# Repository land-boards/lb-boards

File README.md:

lb-boards Designs
=================

land-boards.com - Printed Circuit Board Designs
-----------------------------------------------

Design files are kept here. Most are [Kicad based designs][Kicad].
[Kicad]: http://www.kicad-pcb.org/display/KICAD/KiCad+EDA+Software+Suite/ "Kicad is an open source electronic design suite which includes professional quality schematic capture and board layout tools."

See [our PCB Designs Website][ourWebsite] and our [land-boards Wiki][ourWiki].
[ourWebsite]: http://land-boards.com/content/ "land-boards.com website"
[ourWiki]: http://land-boards.com/blwiki/ "land-boards.com wiki"

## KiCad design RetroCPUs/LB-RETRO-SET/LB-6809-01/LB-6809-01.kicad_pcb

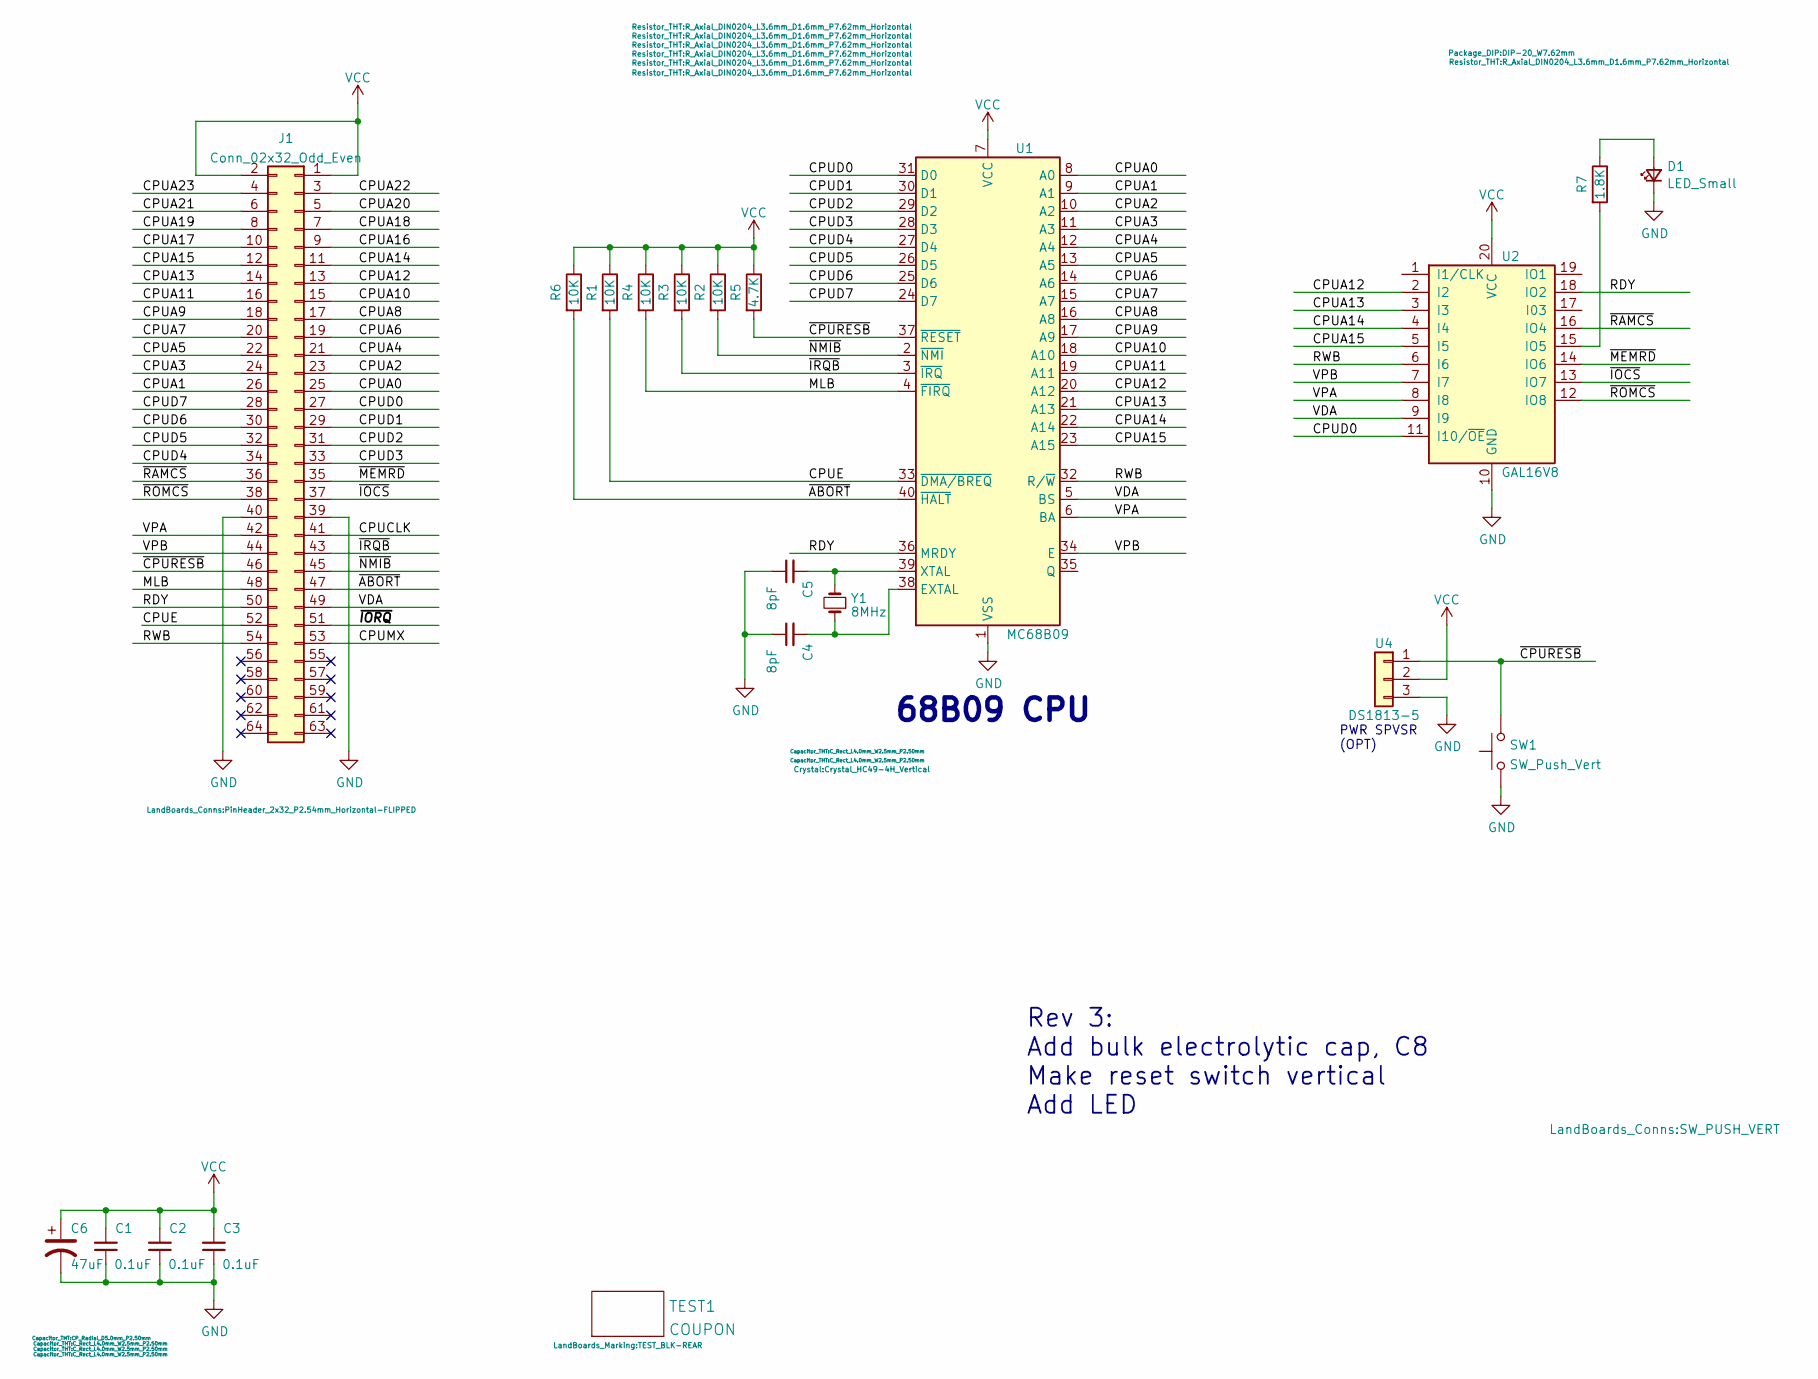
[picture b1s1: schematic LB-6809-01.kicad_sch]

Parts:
C1, C2, C3: 0.1uF; C_Rect_L4.0mm_W2.5mm_P2.50mm
C4, C5: 8pF; C_Rect_L4.0mm_W2.5mm_P2.50mm
C6: 47uF; CP_Radial_D5.0mm_P2.50mm
D1: LED_Small; LED_D5.0mm_Horizontal_O3.81mm_Z9.0mm
J1: Conn_02x32_Odd_Even; PinHeader_2x32_P2.54mm_Horizontal-FLIPPED
R1, R2, R3, R4, R6: 10K; R_Axial_DIN0204_L3.6mm_D1.6mm_P7.62mm_Horizontal
R5: 4.7K; R_Axial_DIN0204_L3.6mm_D1.6mm_P7.62mm_Horizontal
R7: 1.8K; R_Axial_DIN0204_L3.6mm_D1.6mm_P7.62mm_Horizontal
SW1: SW_Push_Vert; SW_PUSH_VERT
TEST1: COUPON; TEST_BLK-REAR
U1: MC68B09; DIP-40_W15.24mm
U2: GAL16V8; DIP-20_W7.62mm
U4: DS1813-5; TO-92
Y1: 8MHz; Crystal_HC49-4H_Vertical

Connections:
/CPUA0: J1.25, U1.8 (A0)
/CPUA1: J1.26, U1.9 (A1)
/CPUA2: J1.23, U1.10 (A2)
/CPUA3: J1.24, U1.11 (A3)
/CPUA4: J1.21, U1.12 (A4)
/CPUA5: J1.22, U1.13 (A5)
/CPUA6: J1.19, U1.14 (A6)
/CPUA7: J1.20, U1.15 (A7)
/CPUA8: J1.17, U1.16 (A8)
/CPUA9: J1.18, U1.17 (A9)
/CPUA10: J1.15, U1.18 (A10)
/CPUA11: J1.16, U1.19 (A11)
/CPUA12: J1.13, U1.20 (A12), U2.2 (I2)
/CPUA13: J1.14, U1.21 (A13), U2.3 (I3)
/CPUA14: J1.11, U1.22 (A14), U2.4 (I4)
/CPUA15: J1.12, U1.23 (A15), U2.5 (I5)
/CPUA16: J1.9
/CPUA17: J1.10
/CPUA18: J1.7
/CPUA19: J1.8
/CPUA20: J1.5
/CPUA21: J1.6
/CPUA22: J1.3
/CPUA23: J1.4
/CPUCLK: J1.41
/CPUD0: J1.27, U1.31 (D0), U2.11 (I10/~OE)
/CPUD1: J1.29, U1.30 (D1)
/CPUD2: J1.31, U1.29 (D2)
/CPUD3: J1.33, U1.28 (D3)
/CPUD4: J1.34, U1.27 (D4)
/CPUD5: J1.32, U1.26 (D5)
/CPUD6: J1.30, U1.25 (D6)
/CPUD7: J1.28, U1.24 (D7)
/CPUE: J1.52, R1.2, U1.33 (~DMA/BREQ)
/CPUMX: J1.53
/MLB: J1.48, R4.2, U1.4 (~FIRQ)
/RDY: J1.50, U1.36 (MRDY), U2.18 (IO2)
/RWB: J1.54, U1.32 (R/~W), U2.6 (I6)
/VDA: J1.49, U1.5 (BS), U2.9 (I9)
/VPA: J1.42, U1.6 (BA), U2.8 (I8)
/VPB: J1.44, U1.34 (E), U2.7 (I7)
/~ABORT: J1.47, R6.2, U1.40 (~HALT)
/~CPURESB: J1.46, R5.2, SW1.2, U1.37 (~RESET), U4.1
/~IOCS: J1.37, U2.13 (IO7)
/~IORQ: J1.51
/~IRQB: J1.43, R3.2, U1.3 (~IRQ)
/~MEMRD: J1.35, U2.14 (IO6)
/~NMIB: J1.45, R2.2, U1.2 (~NMI)
/~RAMCS: J1.36, U2.16 (IO4)
/~ROMCS: J1.38, U2.12 (IO8)
GND: C1.1, C2.1, C3.1, C4.1, C5.1, C6.2, D1.1 (K), J1.39, J1.40, SW1.1, U1.1 (VSS), U2.10 (GND), U4.3
unnamed: D1.2 (A), R7.1
unnamed: C4.2, U1.38 (EXTAL), Y1.1
unnamed: C5.2, U1.39 (XTAL), Y1.2
unnamed: R7.2, U2.15 (IO5)
VCC: C1.2, C2.2, C3.2, C6.1, J1.1, J1.2, R1.1, R2.1, R3.1, R4.1, R5.1, R6.1, U1.7 (VCC), U2.20 (VCC), U4.2

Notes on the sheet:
68B09 CPU
PWR SPVSR (OPT)
Rev 3: Add bulk electrolytic cap, C8 Make reset switch vertical Add LED

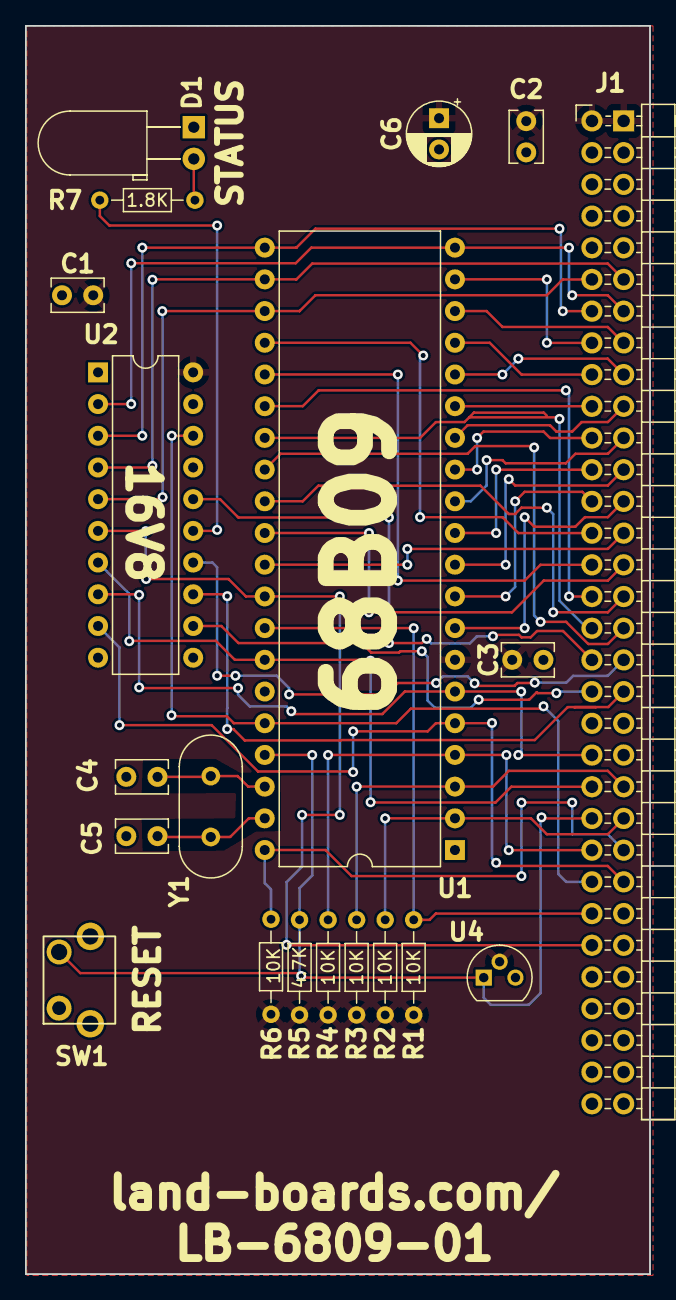
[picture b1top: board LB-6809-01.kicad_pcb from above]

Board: 2 copper layers, 50.0 x 100.0 mm, 21 parts (0 on the bottom side), 45 nets.

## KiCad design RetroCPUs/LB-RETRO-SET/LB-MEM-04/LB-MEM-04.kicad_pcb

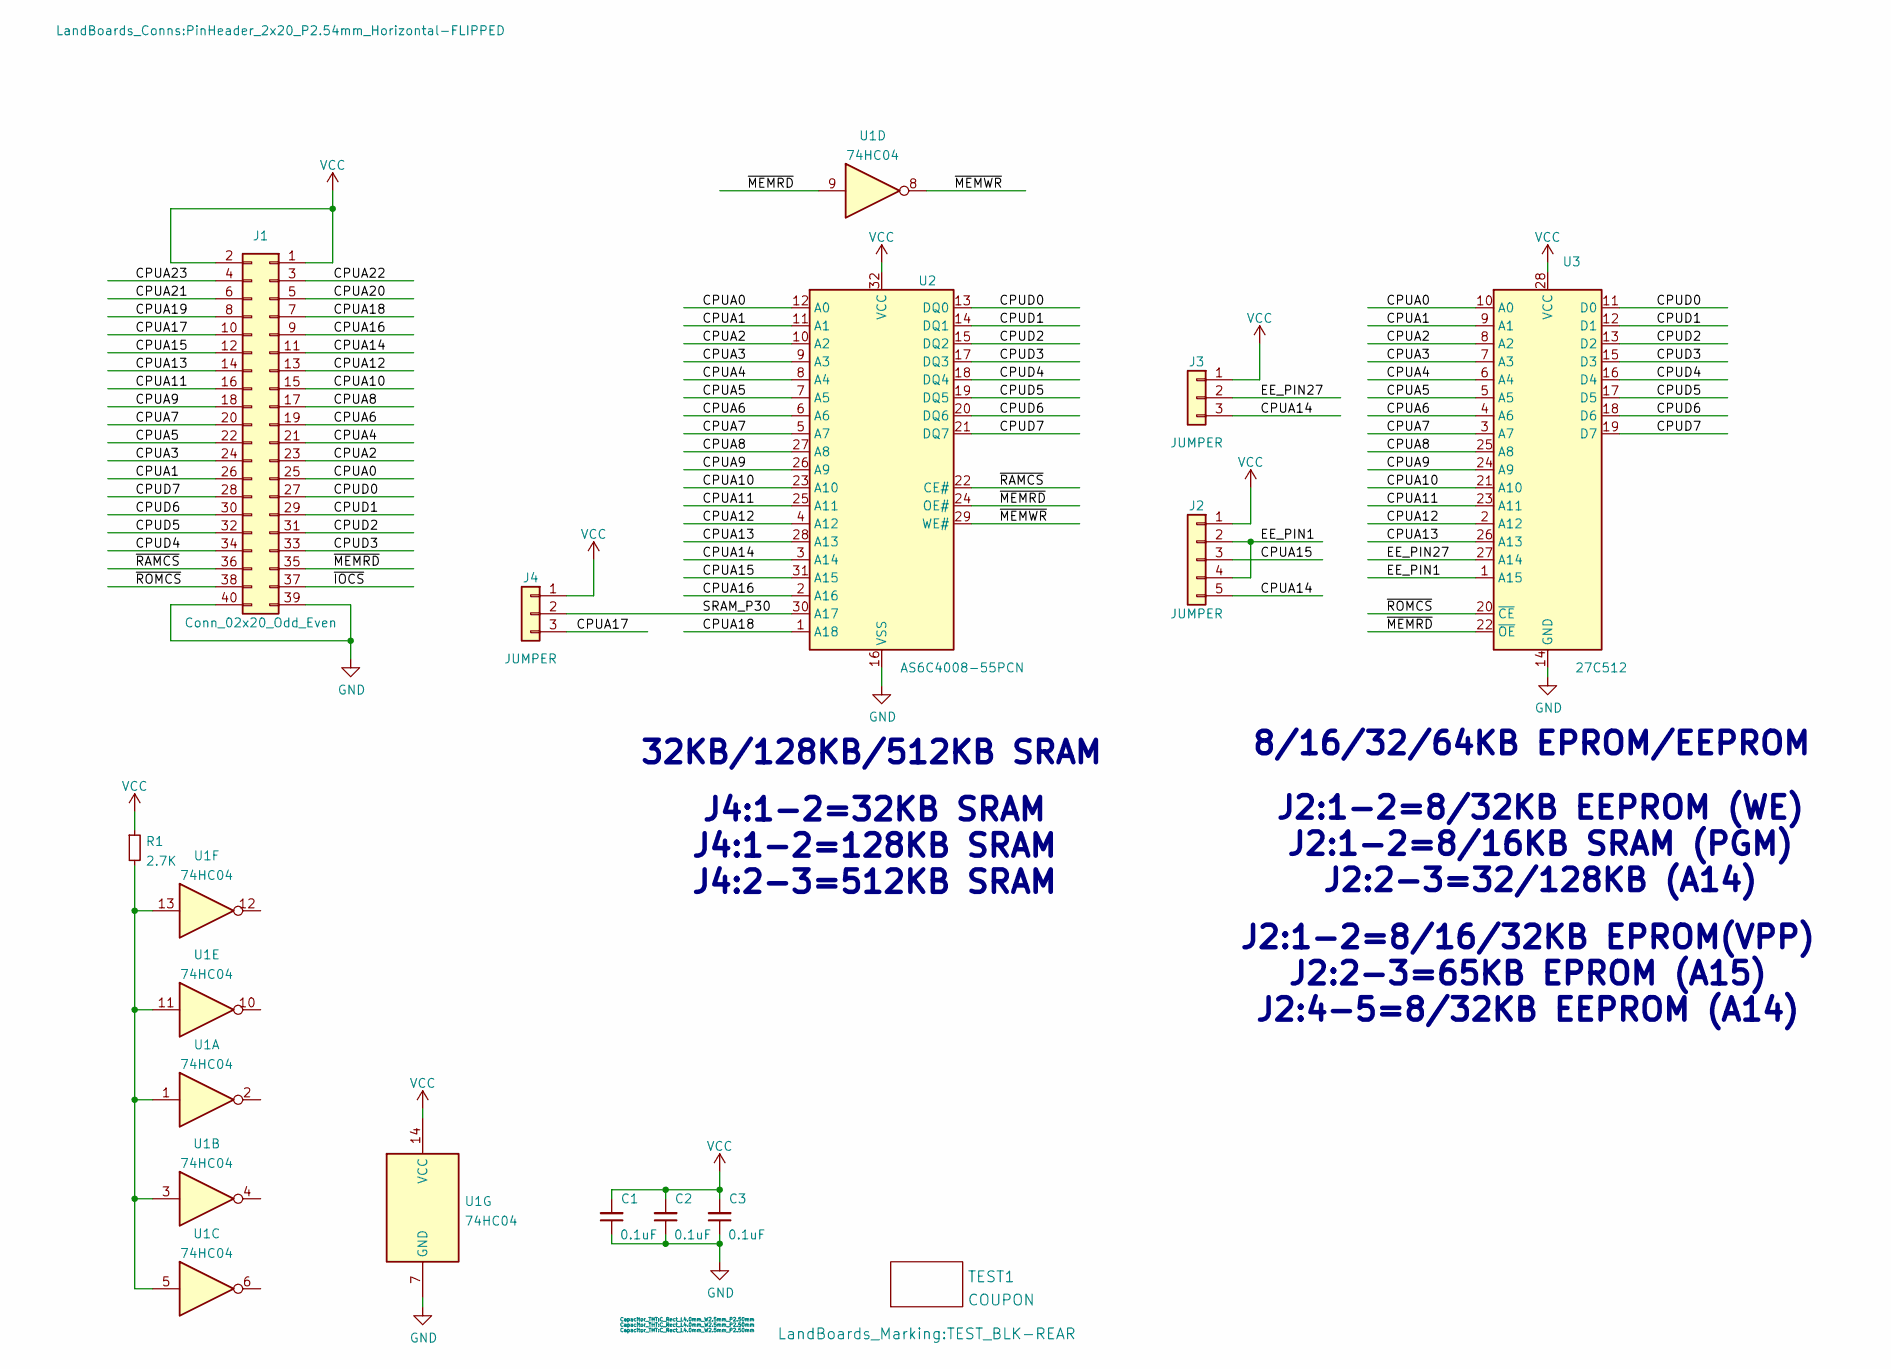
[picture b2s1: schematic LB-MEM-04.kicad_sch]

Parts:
C1, C2, C3: 0.1uF; C_Rect_L4.0mm_W2.5mm_P2.50mm
J1: Conn_02x20_Odd_Even; PinHeader_2x20_P2.54mm_Horizontal-FLIPPED
J2: JUMPER; PinHeader_1x05_P2.54mm_Vertical
J3, J4: JUMPER; PinHeader_1x03_P2.54mm_Vertical
R1: 2.7K; R_Axial_DIN0204_L3.6mm_D1.6mm_P7.62mm_Horizontal
TEST1: COUPON; TEST_BLK-REAR
U1: 74HC04; DIP-14_W7.62mm_LongPads
U2: AS6C4008-55PCN; DIP-32_W15.24mm
U3: 27C512; DIP-28_W15.24mm

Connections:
/CPUA0: J1.25, U2.12 (A0), U3.10 (A0)
/CPUA1: J1.26, U2.11 (A1), U3.9 (A1)
/CPUA2: J1.23, U2.10 (A2), U3.8 (A2)
/CPUA3: J1.24, U2.9 (A3), U3.7 (A3)
/CPUA4: J1.21, U2.8 (A4), U3.6 (A4)
/CPUA5: J1.22, U2.7 (A5), U3.5 (A5)
/CPUA6: J1.19, U2.6 (A6), U3.4 (A6)
/CPUA7: J1.20, U2.5 (A7), U3.3 (A7)
/CPUA8: J1.17, U2.27 (A8), U3.25 (A8)
/CPUA9: J1.18, U2.26 (A9), U3.24 (A9)
/CPUA10: J1.15, U2.23 (A10), U3.21 (A10)
/CPUA11: J1.16, U2.25 (A11), U3.23 (A11)
/CPUA12: J1.13, U2.4 (A12), U3.2 (A12)
/CPUA13: J1.14, U2.28 (A13), U3.26 (A13)
/CPUA14: J1.11, J2.5, J3.3, U2.3 (A14)
/CPUA15: J1.12, J2.3, U2.31 (A15)
/CPUA16: J1.9, U2.2 (A16)
/CPUA17: J1.10, J4.3
/CPUA18: J1.7, U2.1 (A18)
/CPUA19: J1.8
/CPUA20: J1.5
/CPUA21: J1.6
/CPUA22: J1.3
/CPUA23: J1.4
/CPUD0: J1.27, U2.13 (DQ0), U3.11 (D0)
/CPUD1: J1.29, U2.14 (DQ1), U3.12 (D1)
/CPUD2: J1.31, U2.15 (DQ2), U3.13 (D2)
/CPUD3: J1.33, U2.17 (DQ3), U3.15 (D3)
/CPUD4: J1.34, U2.18 (DQ4), U3.16 (D4)
/CPUD5: J1.32, U2.19 (DQ5), U3.17 (D5)
/CPUD6: J1.30, U2.20 (DQ6), U3.18 (D6)
/CPUD7: J1.28, U2.21 (DQ7), U3.19 (D7)
/EE_PIN1: J2.2, J2.4, U3.1 (A15)
/EE_PIN27: J3.2, U3.27 (A14)
/SRAM_P30: J4.2, U2.30 (A17)
/~IOCS: J1.37
/~MEMRD: J1.35, U1.9, U2.24 (OE#), U3.22 (~OE)
/~MEMWR: U1.8, U2.29 (WE#)
/~RAMCS: J1.36, U2.22 (CE#)
/~ROMCS: J1.38, U3.20 (~CE)
GND: C1.1, C2.1, C3.1, J1.39, J1.40, U1.7 (GND), U2.16 (VSS), U3.14 (GND)
unnamed: R1.2, U1.1, U1.3, U1.5, U1.11, U1.13
VCC: C1.2, C2.2, C3.2, J1.1, J1.2, J2.1, J3.1, J4.1, R1.1, U1.14 (VCC), U2.32 (VCC), U3.28 (VCC)

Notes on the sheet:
32KB/128KB/512KB SRAM
J2:1-2=8/32KB EEPROM (WE) J2:1-2=8/16KB SRAM (PGM) J2:2-3=32/128KB (A14)
J2:1-2=8/16/32KB EPROM(VPP) J2:2-3=65KB EPROM (A15) J2:4-5=8/32KB EEPROM (A14)
8/16/32/64KB EPROM/EEPROM
J4:1-2=32KB SRAM J4:1-2=128KB SRAM J4:2-3=512KB SRAM

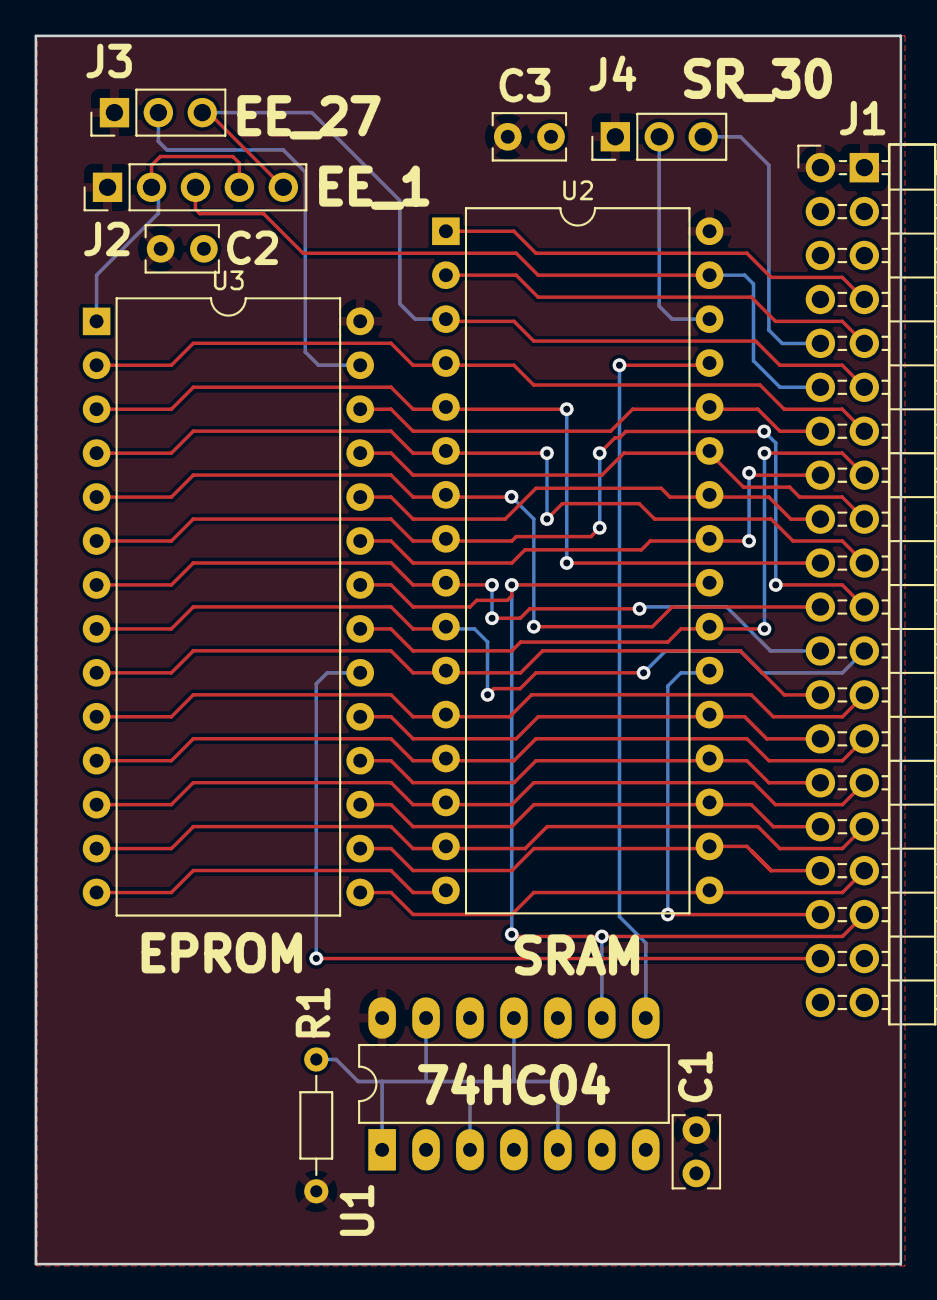
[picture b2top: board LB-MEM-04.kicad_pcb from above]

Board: 2 copper layers, 50.0 x 71.0 mm, 12 parts (0 on the bottom side), 37 nets.

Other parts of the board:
TEST: COUPON; TEST_BLK-REAR

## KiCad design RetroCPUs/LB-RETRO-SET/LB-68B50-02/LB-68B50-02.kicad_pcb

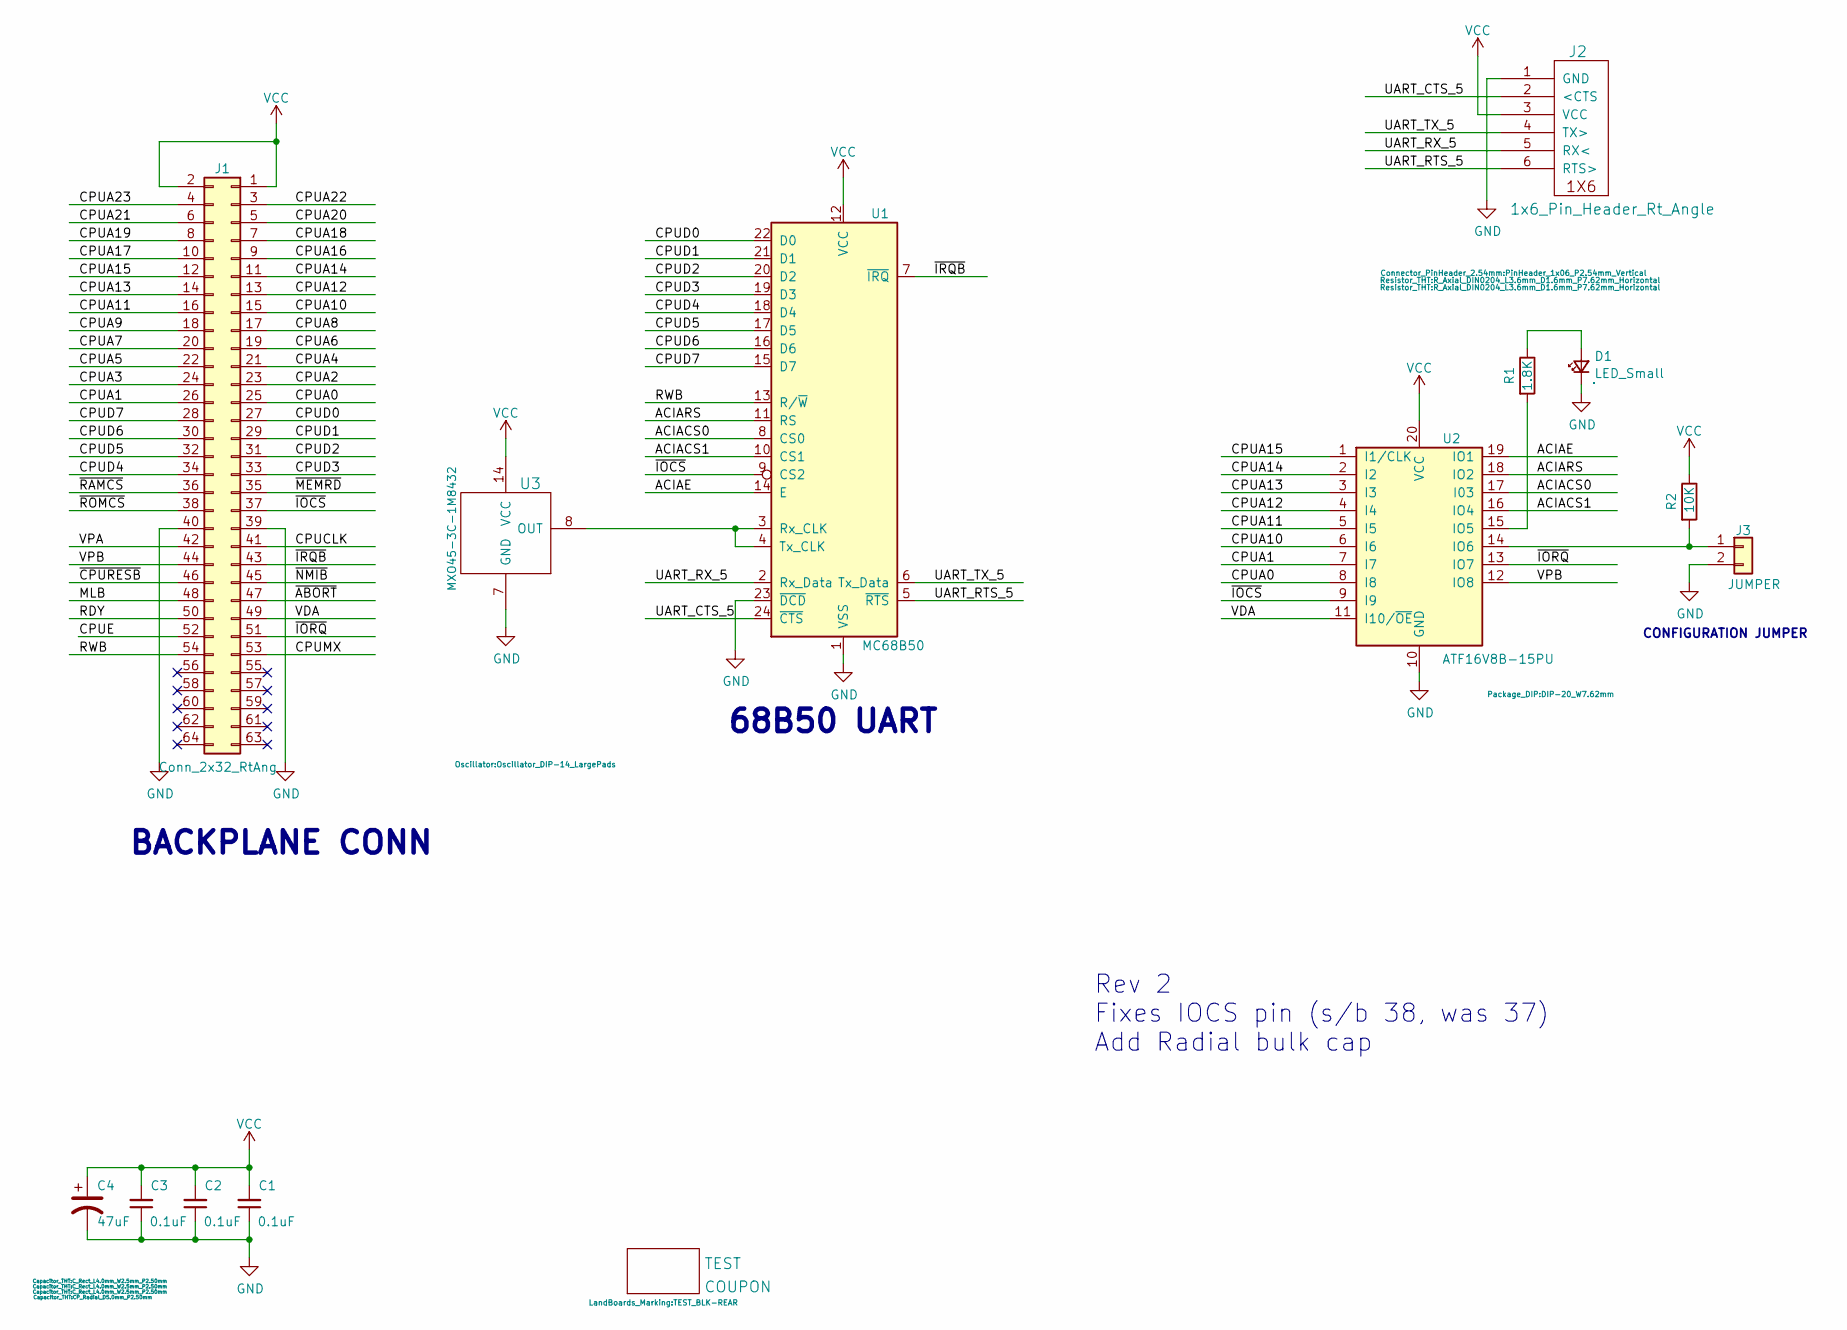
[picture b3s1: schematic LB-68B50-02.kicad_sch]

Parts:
C1, C2, C3: 0.1uF; C_Rect_L4.0mm_W2.5mm_P2.50mm
C4: 47uF; CP_Radial_D5.0mm_P2.50mm
D1: LED_Small; LED_D5.0mm_Horizontal_O3.81mm_Z9.0mm
J1: Conn_2x32_RtAng; PinHeader_2x32_P2.54mm_Horizontal-FLIPPED
J2: 1x6_Pin_Header_Rt_Angle; PinHeader_1x06_P2.54mm_Vertical
J3: JUMPER; PinHeader_1x02_P2.54mm_Vertical
R1: 1.8K; R_Axial_DIN0204_L3.6mm_D1.6mm_P7.62mm_Horizontal
R2: 10K; R_Axial_DIN0204_L3.6mm_D1.6mm_P7.62mm_Horizontal
TEST: COUPON; TEST_BLK-REAR
U1: MC68B50; DIP-24_W15.24mm_LongPads
U2: ATF16V8B-15PU; DIP-20_W7.62mm
U3: MXO45-3C-1M8432; Oscillator_DIP-14_LargePads

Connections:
/ACIACS0: U1.8 (CS0), U2.17 (I03)
/ACIACS1: U1.10 (CS1), U2.16 (IO4)
/ACIAE: U1.14 (E), U2.19 (IO1)
/ACIARS: U1.11 (RS), U2.18 (IO2)
/CPUA0: J1.25, U2.8 (I8)
/CPUA1: J1.26, U2.7 (I7)
/CPUA2: J1.23
/CPUA3: J1.24
/CPUA4: J1.21
/CPUA5: J1.22
/CPUA6: J1.19
/CPUA7: J1.20
/CPUA8: J1.17
/CPUA9: J1.18
/CPUA10: J1.15, U2.6 (I6)
/CPUA11: J1.16, U2.5 (I5)
/CPUA12: J1.13, U2.4 (I4)
/CPUA13: J1.14, U2.3 (I3)
/CPUA14: J1.11, U2.2 (I2)
/CPUA15: J1.12, U2.1 (I1/CLK)
/CPUA16: J1.9
/CPUA17: J1.10
/CPUA18: J1.7
/CPUA19: J1.8
/CPUA20: J1.5
/CPUA21: J1.6
/CPUA22: J1.3
/CPUA23: J1.4
/CPUCLK: J1.41
/CPUD0: J1.27, U1.22 (D0)
/CPUD1: J1.29, U1.21 (D1)
/CPUD2: J1.31, U1.20 (D2)
/CPUD3: J1.33, U1.19 (D3)
/CPUD4: J1.34, U1.18 (D4)
/CPUD5: J1.32, U1.17 (D5)
/CPUD6: J1.30, U1.16 (D6)
/CPUD7: J1.28, U1.15 (D7)
/CPUE: J1.52
/CPUMX: J1.53
/MLB: J1.48
/RDY: J1.50
/RWB: J1.54, U1.13 (R/~W)
/UART_CTS_5: J2.2 (<CTS), U1.24 (~CTS)
/UART_RTS_5: J2.6 (RTS>), U1.5 (~RTS)
/UART_RX_5: J2.5 (RX<), U1.2 (Rx_Data)
/UART_TX_5: J2.4 (TX>), U1.6 (Tx_Data)
/VDA: J1.49, U2.11 (I10/~OE)
/VPA: J1.42
/VPB: J1.44, U2.12 (IO8)
/~ABORT: J1.47
/~CPURESB: J1.46
/~IOCS: J1.37, U1.9 (CS2), U2.9 (I9)
/~IORQ: J1.51, U2.13 (IO7)
/~IRQB: J1.43, U1.7 (~IRQ)
/~MEMRD: J1.35
/~NMIB: J1.45
/~RAMCS: J1.36
/~ROMCS: J1.38
GND: C1.1, C2.1, C3.1, C4.2, D1.1 (K), J1.39, J1.40, J2.1 (GND), J3.2, U1.1 (VSS), U1.23 (~DCD), U2.10 (GND), U3.7 (GND)
unnamed: D1.2 (A), R1.1
unnamed: J3.1, R2.2, U2.14 (IO6)
unnamed: U1.3 (Rx_CLK), U1.4 (Tx_CLK), U3.8 (OUT)
unnamed: R1.2, U2.15 (IO5)
VCC: C1.2, C2.2, C3.2, C4.1, J1.1, J1.2, J2.3 (VCC), R2.1, U1.12 (VCC), U2.20 (VCC), U3.14 (VCC)

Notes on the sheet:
68B50 UART
CONFIGURATION JUMPER
Rev 2 Fixes IOCS pin (s/b 38, was 37) Add Radial bulk cap
BACKPLANE CONN

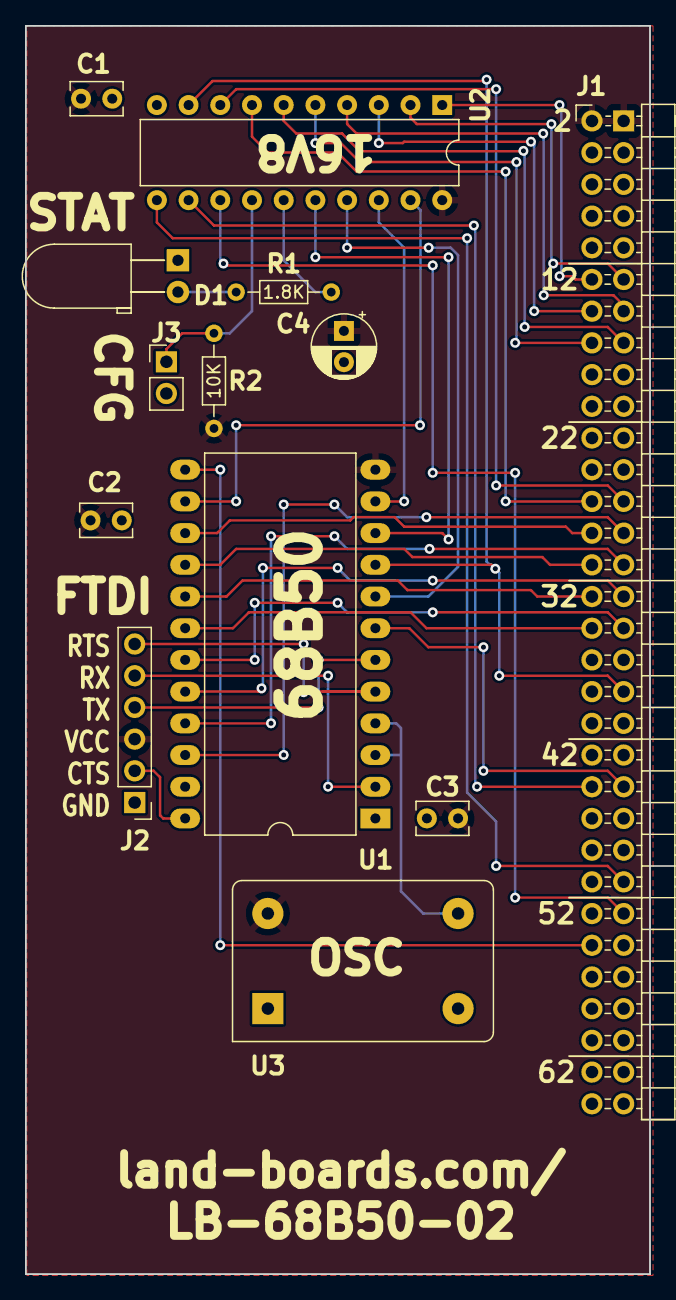
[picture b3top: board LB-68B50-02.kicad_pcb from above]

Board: 2 copper layers, 50.0 x 100.0 mm, 14 parts (0 on the bottom side), 36 nets.

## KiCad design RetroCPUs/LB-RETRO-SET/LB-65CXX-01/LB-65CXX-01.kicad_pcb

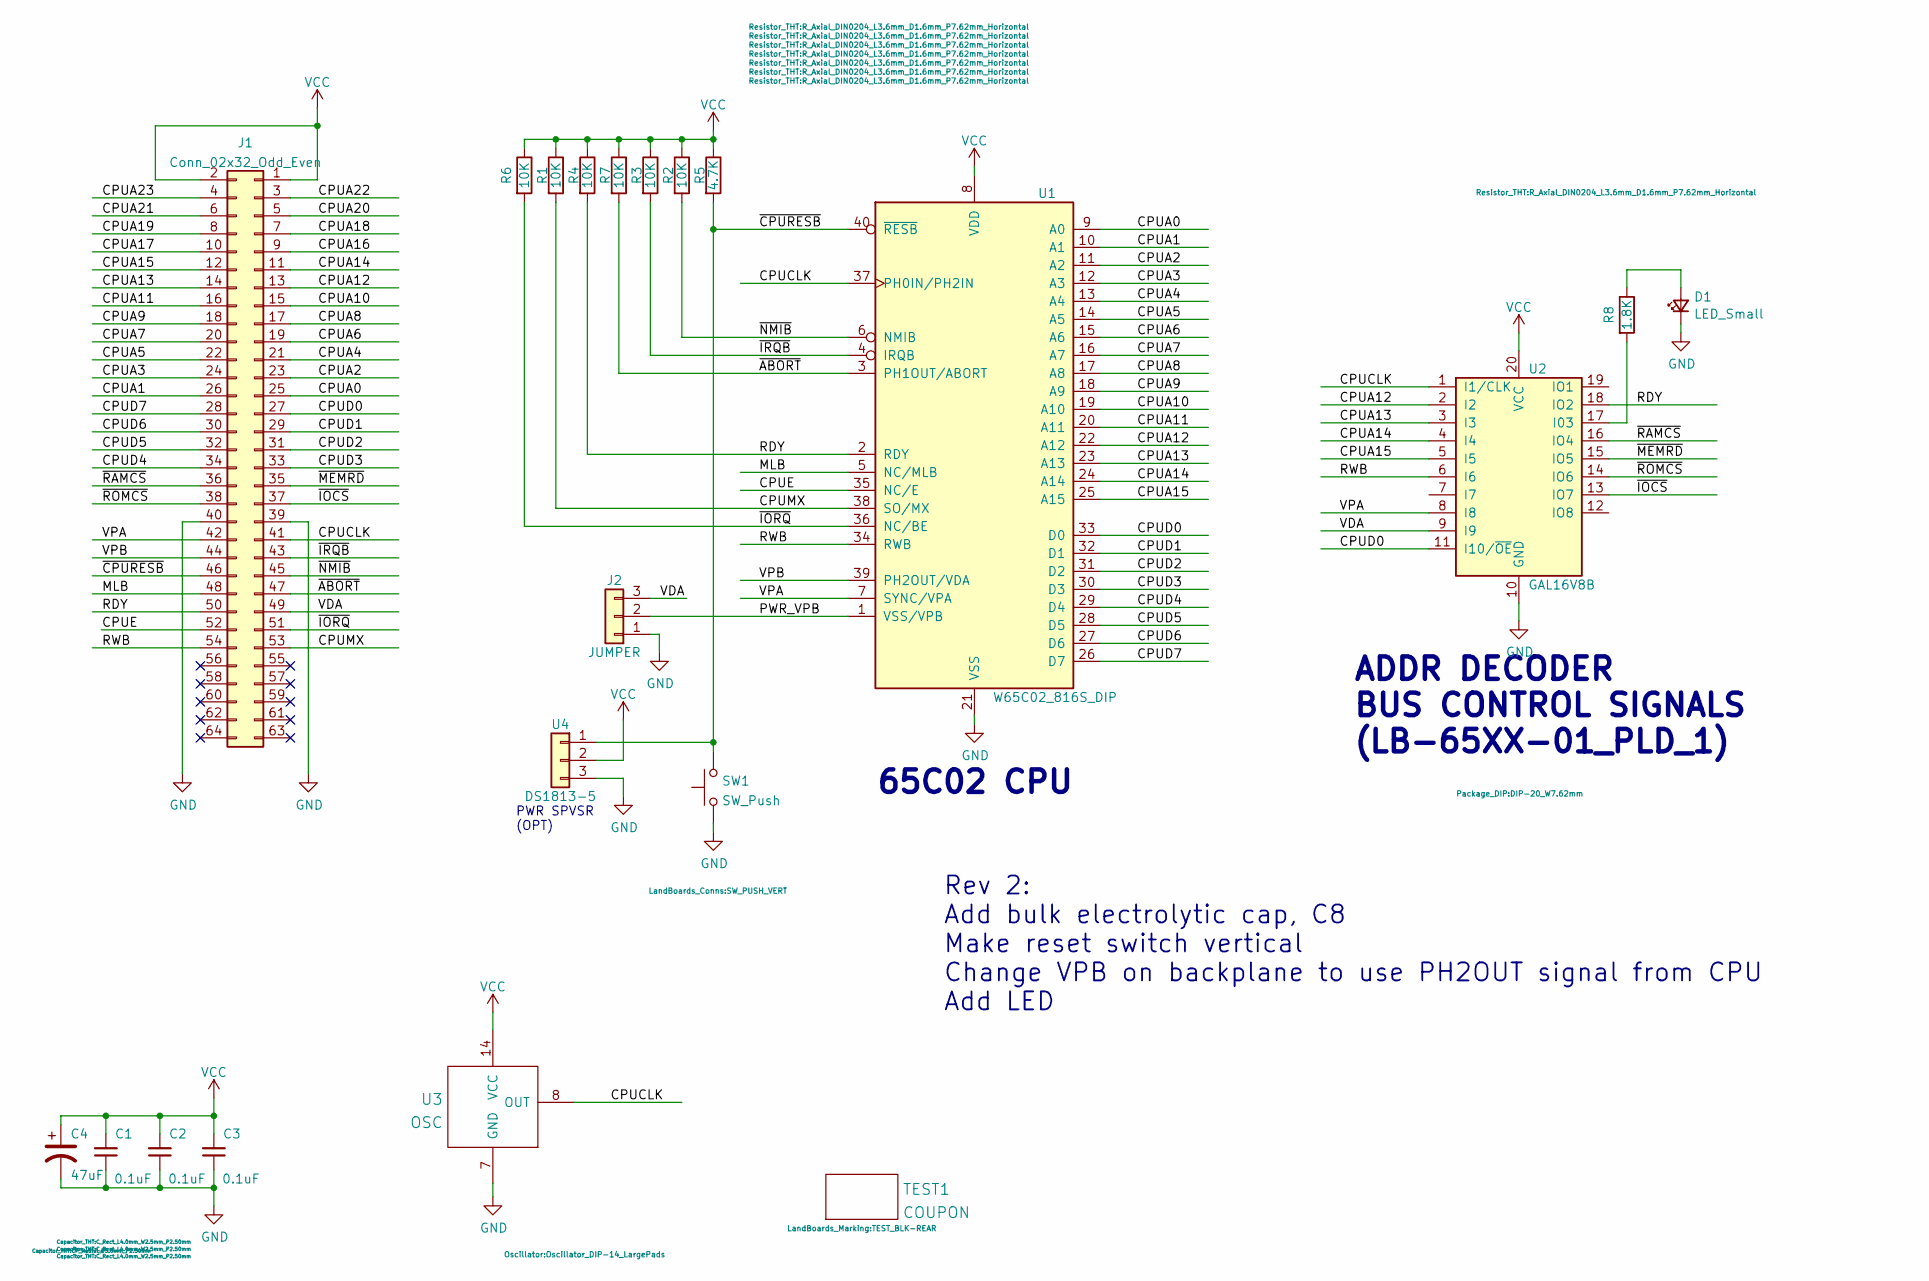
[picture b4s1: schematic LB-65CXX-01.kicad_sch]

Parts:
C1, C2, C3: 0.1uF; C_Rect_L4.0mm_W2.5mm_P2.50mm
C4: 47uF; CP_Radial_D5.0mm_P2.50mm
D1: LED_Small; LED_D5.0mm_Horizontal_O3.81mm_Z9.0mm
J1: Conn_02x32_Odd_Even; PinHeader_2x32_P2.54mm_Horizontal-FLIPPED
J2: JUMPER; PinHeader_1x03_P2.54mm_Vertical
R1, R2, R3, R4, R6, R7: 10K; R_Axial_DIN0204_L3.6mm_D1.6mm_P7.62mm_Horizontal
R5: 4.7K; R_Axial_DIN0204_L3.6mm_D1.6mm_P7.62mm_Horizontal
R8: 1.8K; R_Axial_DIN0204_L3.6mm_D1.6mm_P7.62mm_Horizontal
SW1: SW_Push; SW_PUSH_VERT
TEST1: COUPON; TEST_BLK-REAR
U1: W65C02_816S_DIP; DIP-40_W15.24mm_LongPads
U2: GAL16V8B; DIP-20_W7.62mm
U3: OSC; Oscillator_DIP-14_LargePads
U4: DS1813-5; TO-92

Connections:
/CPUA0: J1.25, U1.9 (A0)
/CPUA1: J1.26, U1.10 (A1)
/CPUA2: J1.23, U1.11 (A2)
/CPUA3: J1.24, U1.12 (A3)
/CPUA4: J1.21, U1.13 (A4)
/CPUA5: J1.22, U1.14 (A5)
/CPUA6: J1.19, U1.15 (A6)
/CPUA7: J1.20, U1.16 (A7)
/CPUA8: J1.17, U1.17 (A8)
/CPUA9: J1.18, U1.18 (A9)
/CPUA10: J1.15, U1.19 (A10)
/CPUA11: J1.16, U1.20 (A11)
/CPUA12: J1.13, U1.22 (A12), U2.2 (I2)
/CPUA13: J1.14, U1.23 (A13), U2.3 (I3)
/CPUA14: J1.11, U1.24 (A14), U2.4 (I4)
/CPUA15: J1.12, U1.25 (A15), U2.5 (I5)
/CPUA16: J1.9
/CPUA17: J1.10
/CPUA18: J1.7
/CPUA19: J1.8
/CPUA20: J1.5
/CPUA21: J1.6
/CPUA22: J1.3
/CPUA23: J1.4
/CPUCLK: J1.41, U1.37 (PH0IN/PH2IN), U2.1 (I1/CLK), U3.8 (OUT)
/CPUD0: J1.27, U1.33 (D0), U2.11 (I10/~OE)
/CPUD1: J1.29, U1.32 (D1)
/CPUD2: J1.31, U1.31 (D2)
/CPUD3: J1.33, U1.30 (D3)
/CPUD4: J1.34, U1.29 (D4)
/CPUD5: J1.32, U1.28 (D5)
/CPUD6: J1.30, U1.27 (D6)
/CPUD7: J1.28, U1.26 (D7)
/CPUE: J1.52, U1.35 (NC/E)
/CPUMX: J1.53, R1.2, U1.38 (SO/MX)
/MLB: J1.48, U1.5 (NC/MLB)
/PWR_VPB: J2.2, U1.1 (VSS/VPB)
/RDY: J1.50, R4.2, U1.2 (RDY), U2.18 (IO2)
/RWB: J1.54, U1.34 (RWB), U2.6 (I6)
/VDA: J1.49, J2.3, U2.9 (I9)
/VPA: J1.42, U1.7 (SYNC/VPA), U2.8 (I8)
/VPB: J1.44, U1.39 (PH2OUT/VDA)
/~ABORT: J1.47, R7.2, U1.3 (PH1OUT/ABORT)
/~CPURESB: J1.46, R5.2, SW1.2, U1.40 (~RESB), U4.1
/~IOCS: J1.37, U2.13 (IO7)
/~IORQ: J1.51, R6.2, U1.36 (NC/BE)
/~IRQB: J1.43, R3.2, U1.4 (IRQB)
/~MEMRD: J1.35, U2.15 (IO5)
/~NMIB: J1.45, R2.2, U1.6 (NMIB)
/~RAMCS: J1.36, U2.16 (IO4)
/~ROMCS: J1.38, U2.14 (IO6)
GND: C1.1, C2.1, C3.1, C4.2, D1.1 (K), J1.39, J1.40, J2.1, SW1.1, U1.21 (VSS), U2.10 (GND), U3.7 (GND), U4.3
unnamed: D1.2 (A), R8.1
unnamed: R8.2, U2.17 (I03)
VCC: C1.2, C2.2, C3.2, C4.1, J1.1, J1.2, R1.1, R2.1, R3.1, R4.1, R5.1, R6.1, R7.1, U1.8 (VDD), U2.20 (VCC), U3.14 (VCC), U4.2

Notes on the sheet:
65C02 CPU
PWR SPVSR (OPT)
Rev 2: Add bulk electrolytic cap, C8 Make reset switch vertical Change VPB on backplane to use PH2OUT signal from CPU Add LED
ADDR DECODER BUS CONTROL SIGNALS (LB-65XX-01_PLD_1)

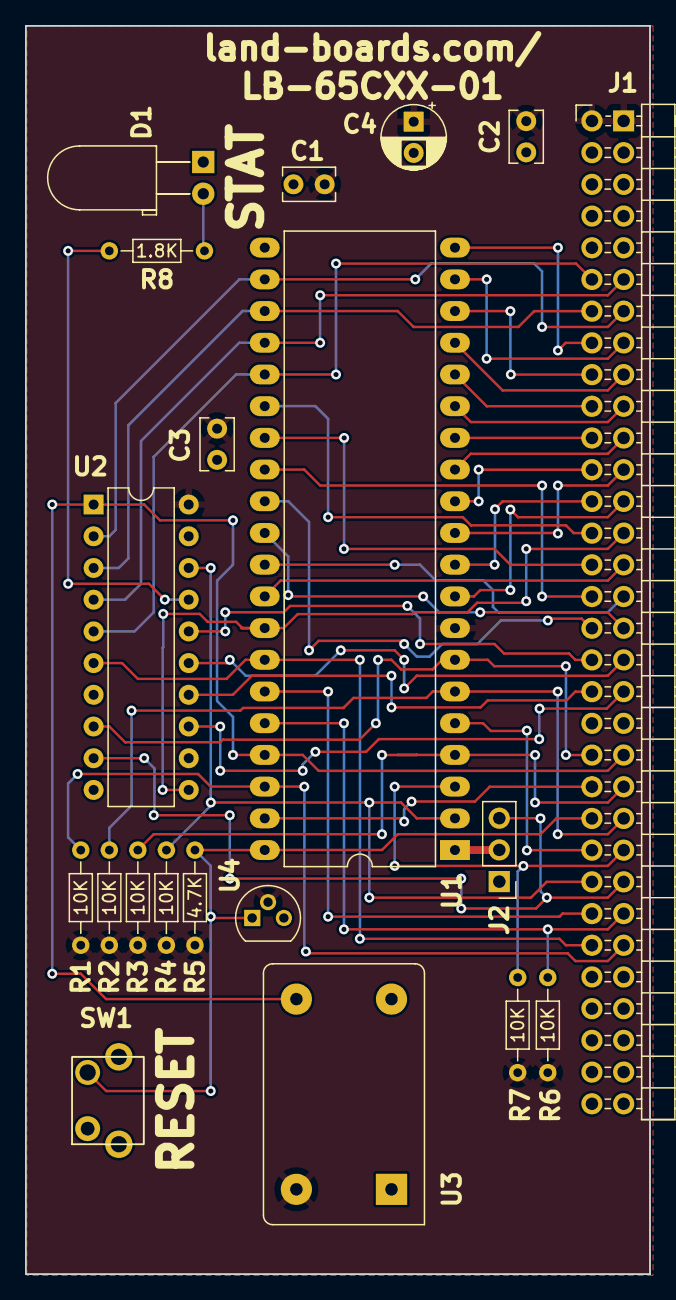
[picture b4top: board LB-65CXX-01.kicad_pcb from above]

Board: 2 copper layers, 50.0 x 100.0 mm, 21 parts (0 on the bottom side), 47 nets.

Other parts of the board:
TEST: COUPON; TEST_BLK-REAR
